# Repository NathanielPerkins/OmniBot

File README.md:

# OmniBot
EESS Modular Robotics Platform

An open source modular robotics platform designed with KiCAD and FreeCAD.
Custom designed Chassis designed to be laser cut/3d printed/CnC Milled. Custom fit stepper motor mounts with embedded motor controller PCB.

Main Processor unit consists of a Raspberry Pi A+ for path planning and general computation. An STM32 ARM microcontroller system controller will handle the stepper motor control via communication with the RPi A+ board and motor controllers. 

1: System Controller

Requirements: The Electronics design require the following footprint libraries for KiCAD

https://github.com/NathanielPerkins/NPFootprints.pretty

2: Mechanical

Chassis design for overall OmniBot frame, and motor mount system

3: Motor Controller

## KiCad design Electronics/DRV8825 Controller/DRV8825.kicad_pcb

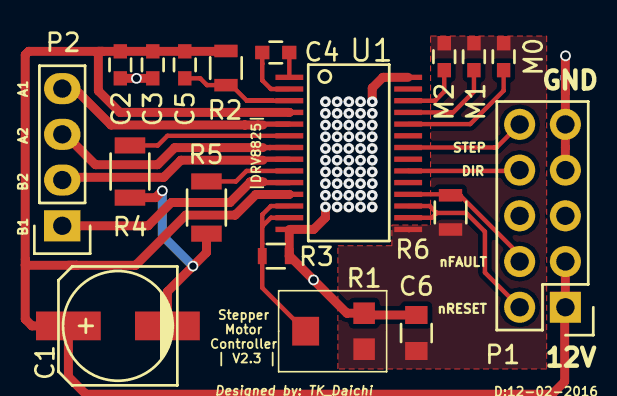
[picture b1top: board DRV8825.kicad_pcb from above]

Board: 2 copper layers, 18 parts (0 on the bottom side), 20 nets.

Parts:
C1: 100uF; c_elec_6.3x7.7
C2, C3, C5: 0.1uF; C_0603
C4: 0.01uF; C_0603
C6: 0.47uF; C_0805
M0, M1, M2: Jumper_NO_Small; C_0603
P1: CONN_01X10; Pin_Header_Straight_2x05
P2: CONN_01X04; Pin_Header_Straight_1x04
R1: 50K Pot; Potentiometer
R2: 1M; R_0805
R3: 30K*; R_0603
R4, R5: 100m; R_1206
R6: 10K; R_0805
U1: DRV8825; DRV-8825_FOOTPRINT

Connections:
+3V3: C6.1, M0.2, M1.2, M2.2, R1.1, R6.1, U1.15
+12V: C1.1, C2.1, C3.1, C5.2, P1.1, P1.3, R2.2, U1.4, U1.11
DIR: P1.8, U1.20
GND: C1.2, C2.2, C3.2, C6.2, P1.7, P1.9, R1.3, R3.2, R4.2, R5.2, U1.14, U1.28
unnamed: C4.1, U1.2
unnamed: C4.2, U1.1
unnamed: C5.1, R2.1, U1.3
unnamed: M2.1, U1.26
unnamed: M1.1, U1.25
unnamed: M0.1, U1.24
unnamed: P2.1, U1.10
unnamed: P2.2, U1.8
unnamed: P2.3, U1.7
unnamed: P2.4, U1.5
unnamed: R1.2, R3.1, U1.12, U1.13
unnamed: R4.1, U1.6
unnamed: R5.1, U1.9
STEP: P1.10, U1.22
nFAULT: P1.4, R6.2, U1.18
nRESET: P1.2, U1.16, U1.17

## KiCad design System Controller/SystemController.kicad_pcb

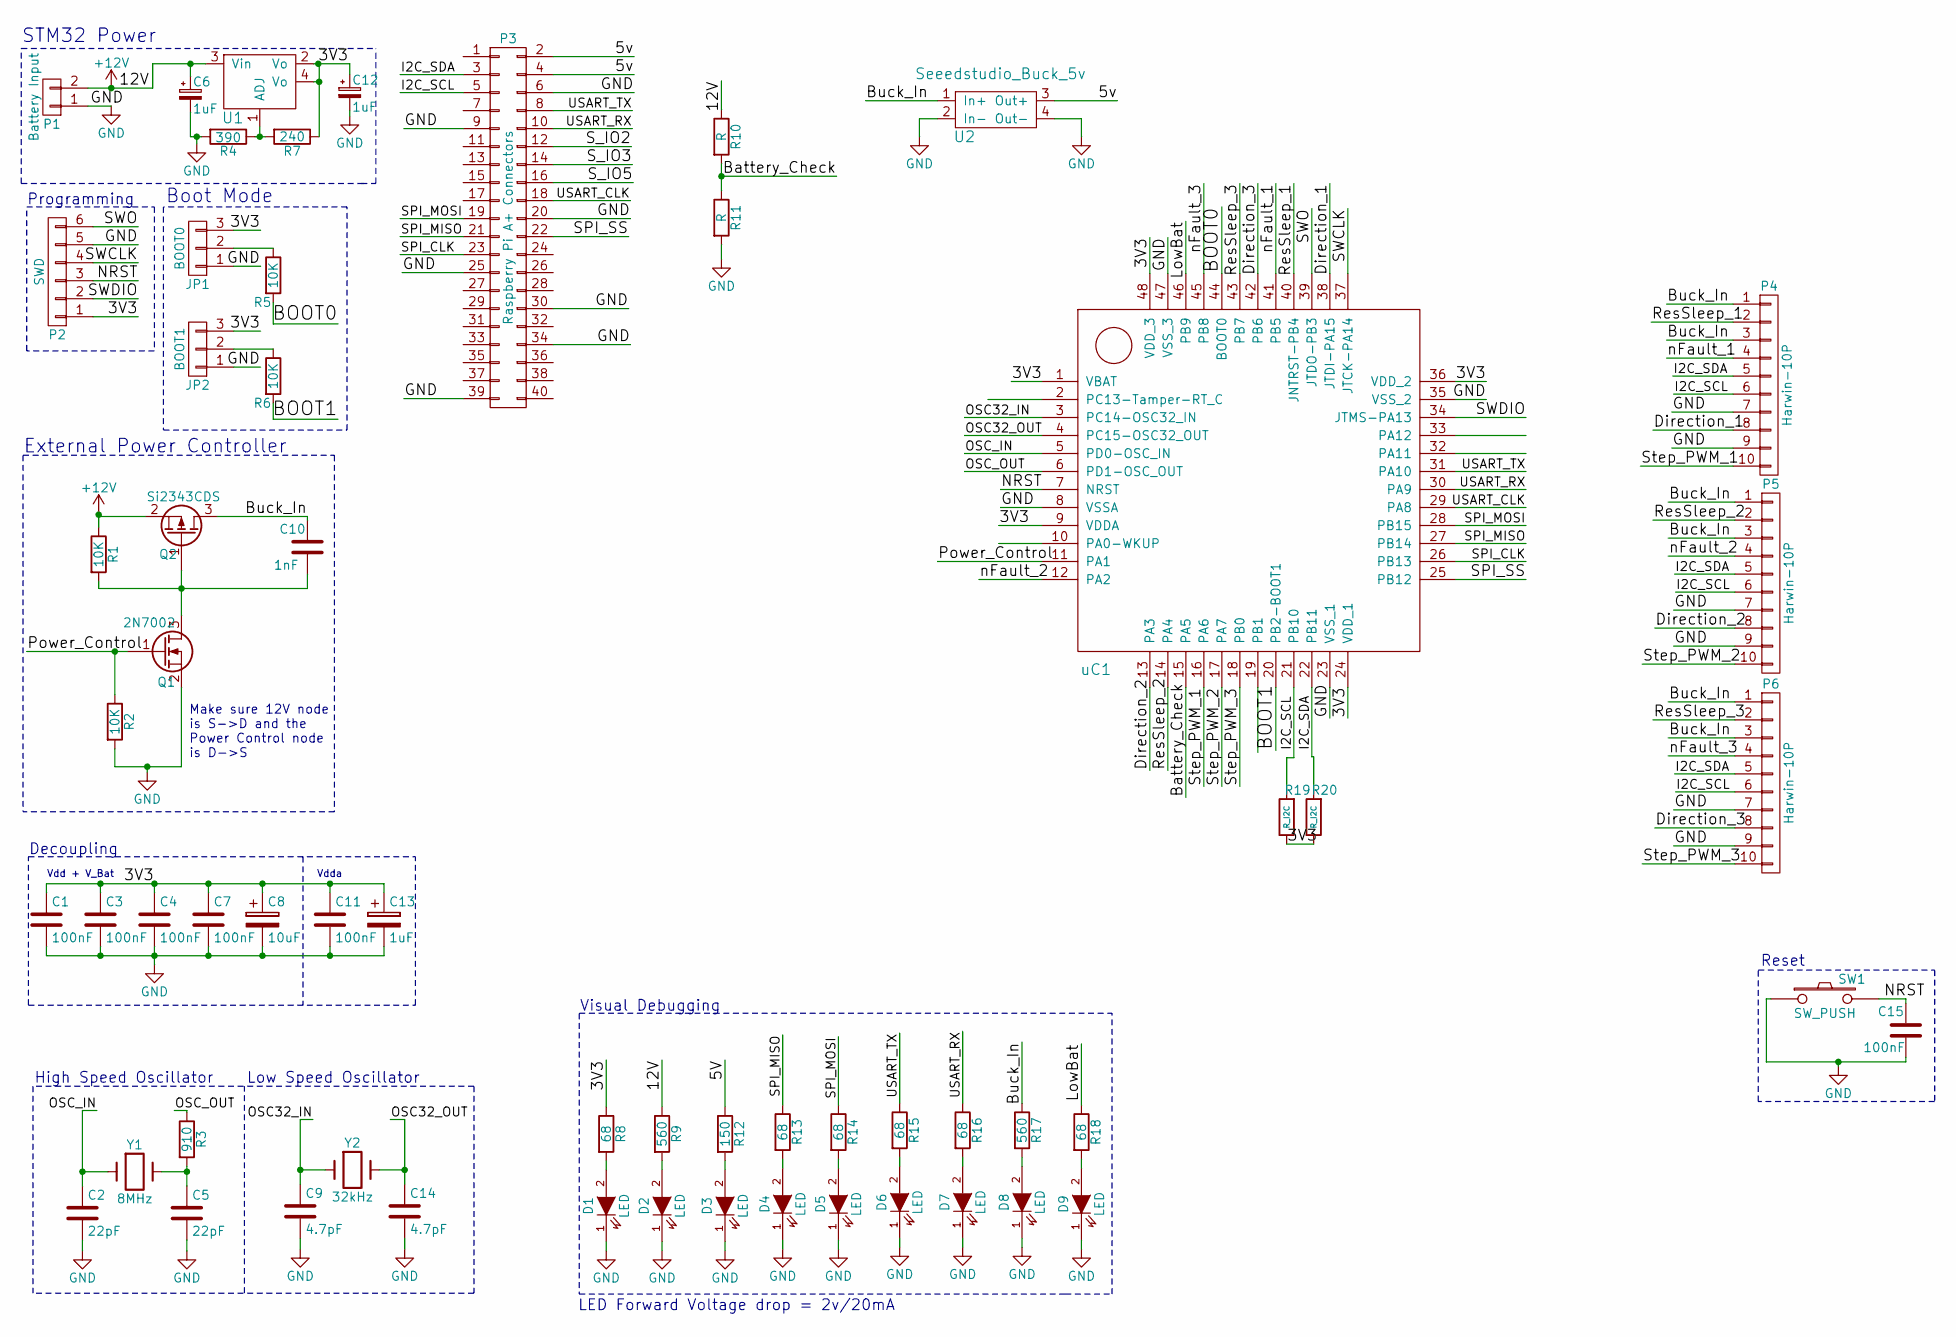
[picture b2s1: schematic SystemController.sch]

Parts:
C1, C3, C4, C7, C11, C15: 100nF; C_0805
C2, C5: 22pF; C_0805
C6, C12, C13: 1uF; C_0805
C8: 10uF; C_0805
C9, C14: 4.7pF; C_0603
C10: 1nF; C_0805
D1, D2, D3, D4, D5, D6, D7, D8, D9: LED; LED_0805
JP1: BOOT0; Pin_Header_Straight_1x03
JP2: BOOT1; Pin_Header_Straight_1x03
P1: Battery Input; Molex_MicroFit_3.0_RightAngle
P2: SWD; Tag-Connect_6P_Leads
P3: Raspberry Pi A+ Connectors; Raspberry_Pi_A+
P4, P5, P6: Harwin-10P; Pin_Header_Straight_2x05
Q1: 2N7002; SOT-23
Q2: Si2343CDS; SOT-23
R1, R2, R5, R6: 10K; R_0805_HandSoldering
R3: 910; R_0805_HandSoldering
R4: 390; R_0805_HandSoldering
R7: 240; R_0805_HandSoldering
R8, R13, R14, R15, R16, R18: 68; R_0603_HandSoldering
R9, R17: 560; R_0603_HandSoldering
R10, R11: R; R_0603_HandSoldering
R12: 150; R_0603_HandSoldering
R19, R20: R_I2C; R_0805_HandSoldering
SW1: SW_PUSH; B3F-1025_Tactile_Switch
U1: LM317; SOT-223
U2: Seeedstudio_Buck_5v; Seeedstudio_5V_Buck
Y1: 8MHz; HC49SDLF_Crystal_Series
Y2: 32kHz; QTC3_Series_Crystal
uC1: STM32F103CBT6; LQFP-48_7x7mm_Pitch0.5mm

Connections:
+12V: C6.1, P1.2, Q2.2 (S), R1.1, R9.1, R10.1, U1.3 (Vin)
/3V3: C1.1, C3.1, C4.1, C7.1, C8.1, C11.1, C12.1, C13.1, JP1.3, JP2.3, P2.1, R7.1, R8.1, R19.1, R20.1, U1.2 (Vo), U1.4 (Vo), uC1.1 (VBAT), uC1.9 (VDDA), uC1.24 (VDD_1), uC1.36 (VDD_2), uC1.48 (VDD_3)
/5V: P3.2, P3.4, R12.1, U2.3 (Out+)
/BOOT0: R5.2, uC1.44 (BOOT0)
/BOOT1: R6.2, uC1.20 (PB2-BOOT1)
/Battery_Check: R10.2, R11.1, uC1.15 (PA5)
/Buck_In: C10.1, P4.1, P4.3, P5.1, P5.3, P6.1, P6.3, Q2.3 (D), R17.1, U2.1 (In+)
/Direction_1: P4.8, uC1.38 (JTDI-PA15)
/Direction_2: P5.8, uC1.13 (PA3)
/Direction_3: P6.8, uC1.42 (PB6)
/I2C_SCL: P3.5, P4.6, P5.6, P6.6, R19.2, uC1.21 (PB10)
/I2C_SDA: P3.3, P4.5, P5.5, P6.5, R20.2, uC1.22 (PB11)
/LowBat: R18.1, uC1.46 (PB9)
/NRST: C15.1, P2.3, SW1.2, uC1.7 (NRST)
/OSC32_IN: C9.1, Y2.1, uC1.3 (PC14-OSC32_IN)
/OSC32_OUT: C14.1, Y2.2, uC1.4 (PC15-OSC32_OUT)
/OSC_IN: C2.1, Y1.1, uC1.5 (PD0-OSC_IN)
/OSC_OUT: R3.1, uC1.6 (PD1-OSC_OUT)
/Power_Control: Q1.1 (G), R2.1, uC1.11 (PA1)
/ResSleep_1: P4.2, uC1.40 (JNTRST-PB4)
/ResSleep_2: P5.2, uC1.14 (PA4)
/ResSleep_3: P6.2, uC1.43 (PB7)
/SPI_CLK: P3.23, uC1.26 (PB13)
/SPI_MISO: P3.21, R13.1, uC1.27 (PB14)
/SPI_MOSI: P3.19, R14.1, uC1.28 (PB15)
/SPI_SS: P3.22, uC1.25 (PB12)
/SWCLK: P2.4, uC1.37 (JTCK-PA14)
/SWDIO: P2.2, uC1.34 (JTMS-PA13)
/SWO: P2.6, uC1.39 (JTDO-PB3)
/S_IO2: P3.12
/S_IO3: P3.14
/S_IO5: P3.16
/Step_PWM_1: P4.10, uC1.16 (PA6)
/Step_PWM_2: P5.10, uC1.17 (PA7)
/Step_PWM_3: P6.10, uC1.18 (PB0)
/USART_CLK: P3.18, uC1.29 (PA8)
/USART_RX: P3.10, R16.1, uC1.30 (PA9)
/USART_TX: P3.8, R15.1, uC1.31 (PA10)
/nFault_1: P4.4, uC1.41 (PB5)
/nFault_2: P5.4, uC1.12 (PA2)
/nFault_3: P6.4, uC1.45 (PB8)
GND: C1.2, C2.2, C3.2, C4.2, C5.2, C6.2, C7.2, C8.2, C9.2, C11.2, C12.2, C13.2, C14.2, C15.2, D1.1 (K), D2.1 (K), D3.1 (K), D4.1 (K), D5.1 (K), D6.1 (K), D7.1 (K), D8.1 (K), D9.1 (K), JP1.1, JP2.1, P1.1, P2.5, P3.6, P3.9, P3.20, P3.25, P3.30, P3.34, P3.39, P4.7, P4.9, P5.7, P5.9, P6.7, P6.9, Q1.2 (S), R2.2, R4.2, R11.2, SW1.1, U2.2 (In-), U2.4 (Out-), uC1.8 (VSSA), uC1.23 (VSS_1), uC1.35 (VSS_2), uC1.47 (VSS_3)
unnamed: C5.1, R3.2, Y1.2
unnamed: C10.2, Q1.3 (D), Q2.1 (G), R1.2
unnamed: D1.2 (A), R8.2
unnamed: D2.2 (A), R9.2
unnamed: D3.2 (A), R12.2
unnamed: D4.2 (A), R13.2
unnamed: D5.2 (A), R14.2
unnamed: D6.2 (A), R15.2
unnamed: D7.2 (A), R16.2
unnamed: D8.2 (A), R17.2
unnamed: D9.2 (A), R18.2
unnamed: JP1.2, R5.1
unnamed: JP2.2, R6.1
unnamed: R4.1, R7.2, U1.1 (ADJ)

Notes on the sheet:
STM32 Power
Boot Mode
External Power Controller
Make sure 12V node is S->D and the Power Control node is D->S
Vdd + V_Bat
Vdda
Decoupling
High Speed Oscillator
Low Speed Oscillator
Reset
Programming
Visual Debugging
LED Forward Voltage drop = 2v/20mA

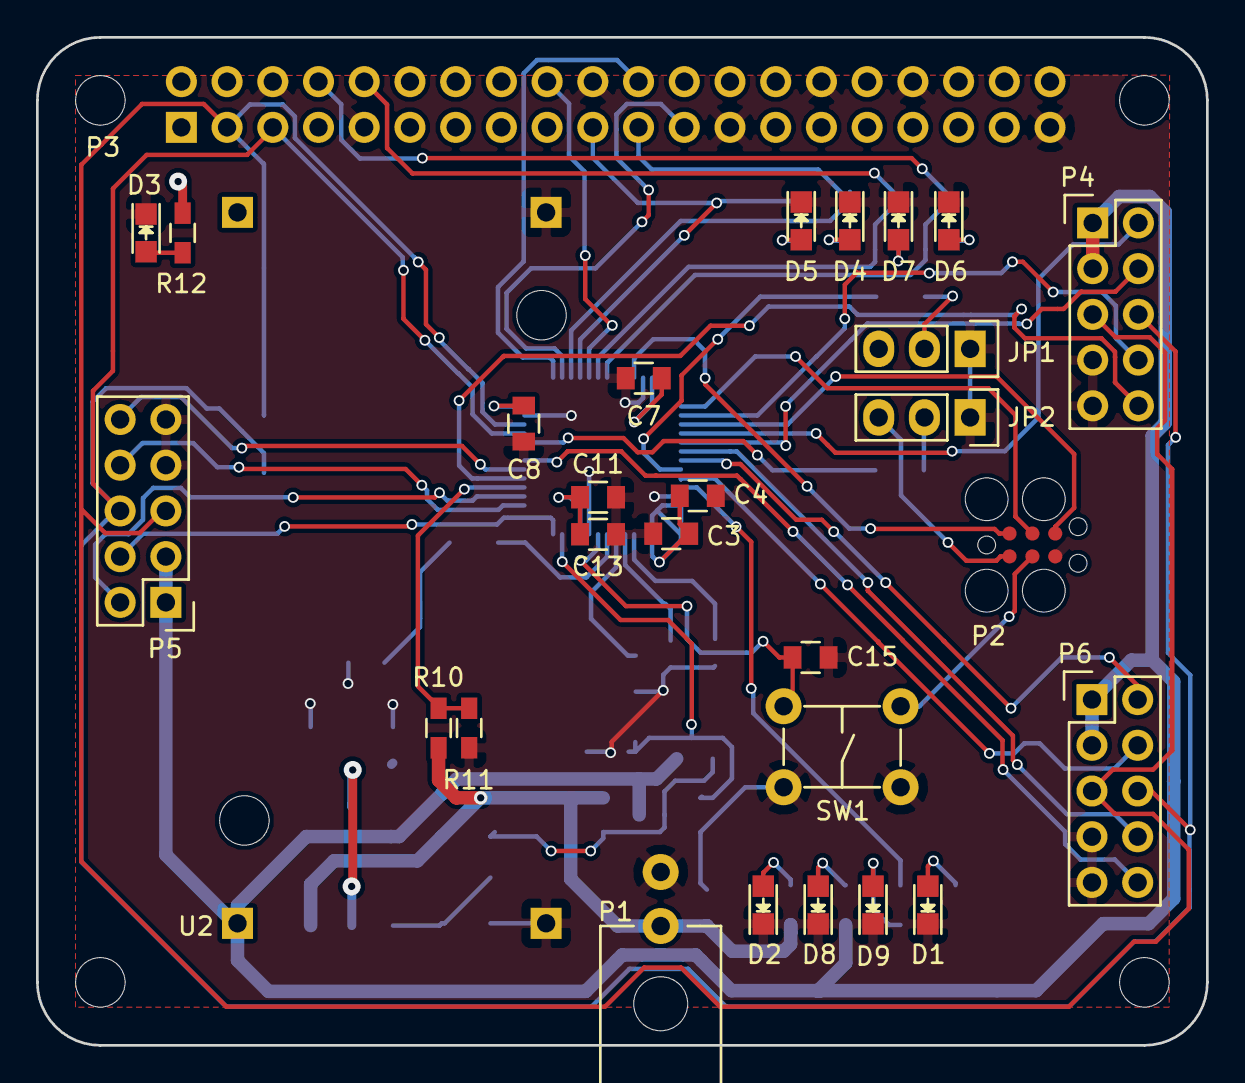
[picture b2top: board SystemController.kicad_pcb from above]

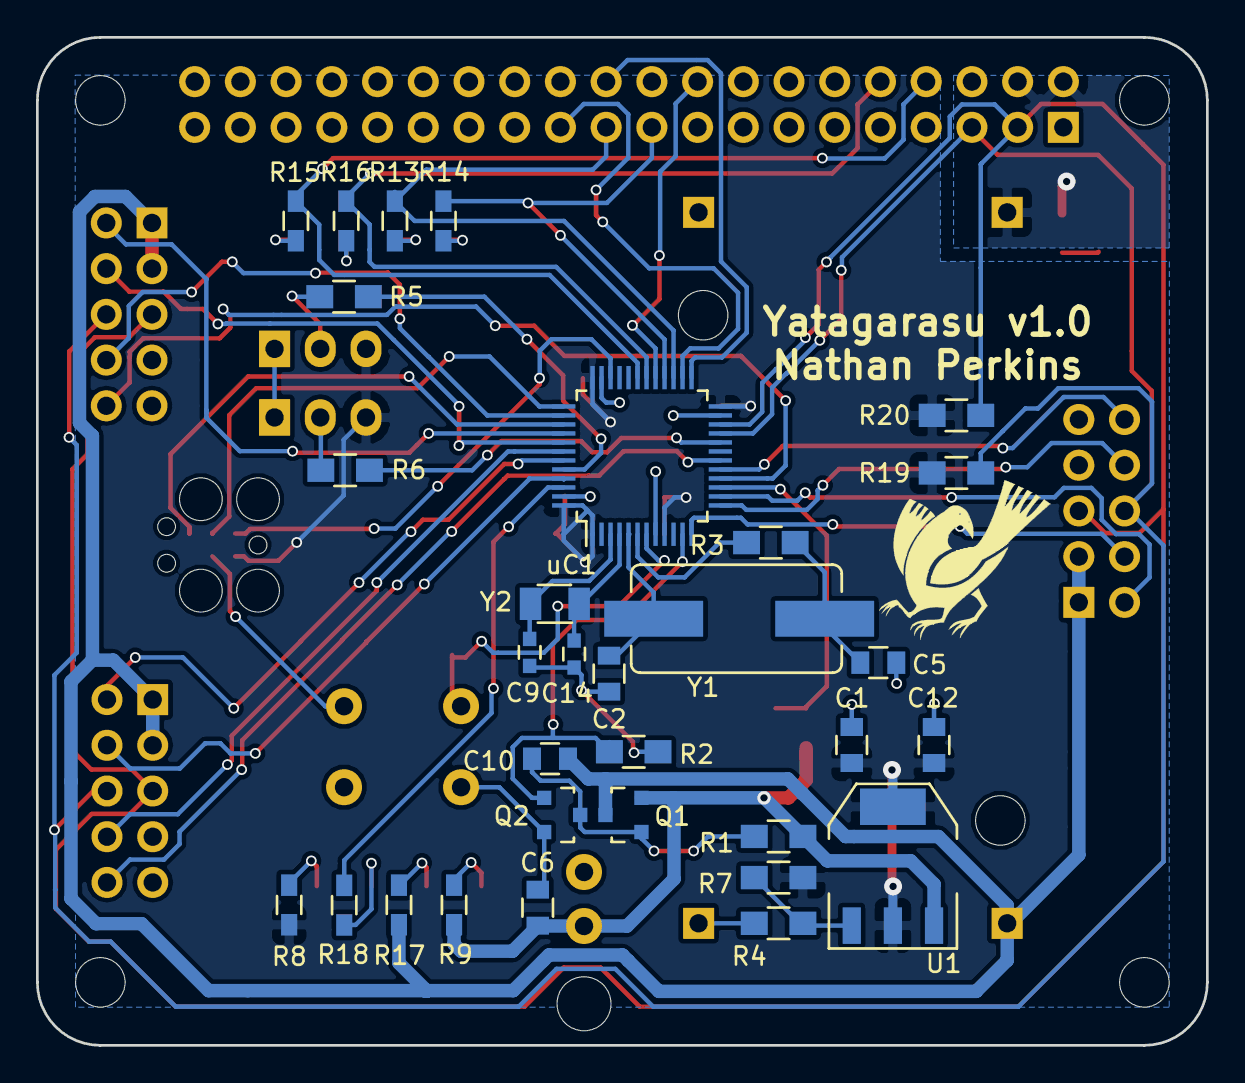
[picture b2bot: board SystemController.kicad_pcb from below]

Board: 2 copper layers, 65.0 x 56.0 mm, 60 parts (31 on the bottom side), 53 nets.

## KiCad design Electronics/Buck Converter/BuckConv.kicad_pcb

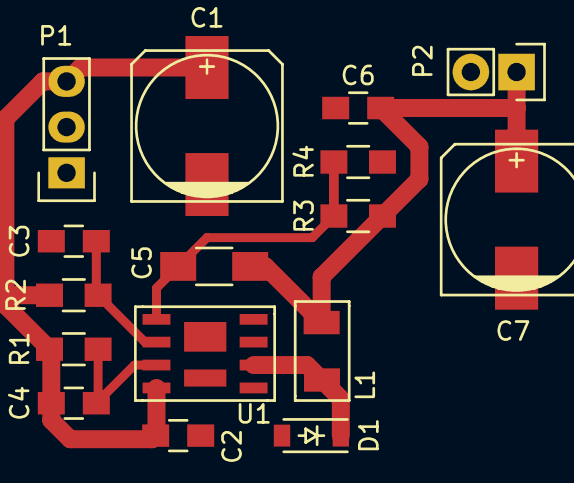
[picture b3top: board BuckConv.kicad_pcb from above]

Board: 2 copper layers, 16 parts (0 on the bottom side), 7 nets.

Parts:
C1: 470u; c_elec_8x10
C2, C3, C4, C6: 0.1u; C_0805_HandSoldering
C5: 5600p; C_1206_HandSoldering
C7: 470u; c_elec_8x10.5
D1: D_Schottky; SOD-123
L1: INDUCTOR; Inductor1
P1: CONN_01X03; Pin_Header_Straight_1x03
P2: CONN_01X02; Socket_Strip_Straight_1x02
R1: 3.9k; R_0805_HandSoldering
R2: 100k; R_0805_HandSoldering
R3: 6.8k; R_0805_HandSoldering
R4: 1.3k; R_0805_HandSoldering
U1: AP_1539; BuckConv

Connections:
/Output: C5.1, C6.1, C7.1, L1.1, P2.1, R3.1
/OutputPower: D1.1, L1.2, U1.6
/vcc-in: C1.1, C2.1, C4.1, P1.3, R1.1, R2.1, U1.4
GND: C1.2, C2.2, C3.2, C6.2, C7.2, D1.2, P1.1, P2.2, R4.2, U1.7
unnamed: C3.1, R2.2, U1.2
unnamed: C4.2, R1.2, U1.3
unnamed: C5.2, R3.2, R4.1, U1.1

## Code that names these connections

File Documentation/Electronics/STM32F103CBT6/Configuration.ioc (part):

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Mcu.Name=STM32F103C(8-B)Tx
Mcu.Package=LQFP48
Mcu.UserName=STM32F103CBTx
PA10.Mode=Synchronous
PA10.Signal=USART1_RX
PA11.Mode=Device
PA11.Signal=USB_DM
PA12.Mode=Device
PA12.Signal=USB_DP
PA13.Mode=Trace_Asynchronous_SW
PA13.Signal=SYS_JTMS-SWDIO
PA14.Mode=Trace_Asynchronous_SW
PA14.Signal=SYS_JTCK-SWCLK
PA15.Signal=GPIO_Output
PA2.Signal=GPIO_Input
PA3.Signal=GPIO_Input
PA4.Signal=GPIO_Input
PA5.Signal=ADCx_IN5
PA6.Signal=S_TIM3_CH1
PA7.Signal=S_TIM3_CH2
PA8.Mode=Synchronous
PA8.Signal=USART1_CK
PA9.Mode=Synchronous
PA9.Signal=USART1_TX
PB0.Signal=S_TIM3_CH3
PB10.Mode=I2C
PB10.Signal=I2C2_SCL
PB11.Mode=I2C
PB11.Signal=I2C2_SDA
PB12.Mode=NSS_Signal_Hard
PB12.Signal=SPI2_NSS
PB13.Mode=Full_Duplex_Slave
PB13.Signal=SPI2_SCK
PB14.Mode=Full_Duplex_Slave
PB14.Signal=SPI2_MISO
PB15.Mode=Full_Duplex_Slave
PB15.Signal=SPI2_MOSI
PB3.Mode=Trace_Asynchronous_SW
PB3.Signal=SYS_JTDO-TRACESWO
PB4.Signal=GPIO_Output
PB5.Signal=GPIO_Output
PB6.Signal=GPIO_Output
PB7.Signal=GPIO_Output
PB8.Signal=GPIO_Output
PC14-OSC32_IN.Mode=LSE-External-Oscillator
PC14-OSC32_IN.Signal=RCC_OSC32_IN
PC15-OSC32_OUT.Mode=LSE-External-Oscillator
PC15-OSC32_OUT.Signal=RCC_OSC32_OUT
PD0-OSC_IN.Mode=HSE-External-Oscillator
PD0-OSC_IN.Signal=RCC_OSC_IN
PD1-OSC_OUT.Mode=HSE-External-Oscillator
PD1-OSC_OUT.Signal=RCC_OSC_OUT

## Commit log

2016-02-24 Update dependancies
2016-02-24 formatting
2016-02-24 Initial Commit of backlog
2016-03-18 Refactoring local repository.
2016-03-18 Re-organizing repo
2016-03-18 Screenshots and update Readme
2016-03-18 Adding BOM
2016-03-18 Umm 1.0
    Pushed?
2016-03-18 Revert "Umm 1.0"
    This reverts commit cc9c9a6458a31b3baf7c23216ac2a969229ed4a6.
2016-03-18 I did something
2016-03-18 I did somethign silly
2016-03-18 Reverting Tobi's Madness
2016-03-18 Updating Readme
    Better Description
2016-03-18 Formatting Issues Readme
    bloody formatting
2016-03-19 Updating Design Justification
    removing redundant info or incorrect information
2016-03-19 PCB Tidy-up
    Slight changes to SystemController PCB
2016-03-20 WIP: System-Controller Power Redesign
2016-05-28 Create Buck Converter
2016-05-28 Buck Converter addition
    Addition of the buck converter prototype design to be later implemented into the final module. Using the AP1539 chip.
